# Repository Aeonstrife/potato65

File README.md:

# potato65

PCB, Plate and Case files for Potato65 keyboard.

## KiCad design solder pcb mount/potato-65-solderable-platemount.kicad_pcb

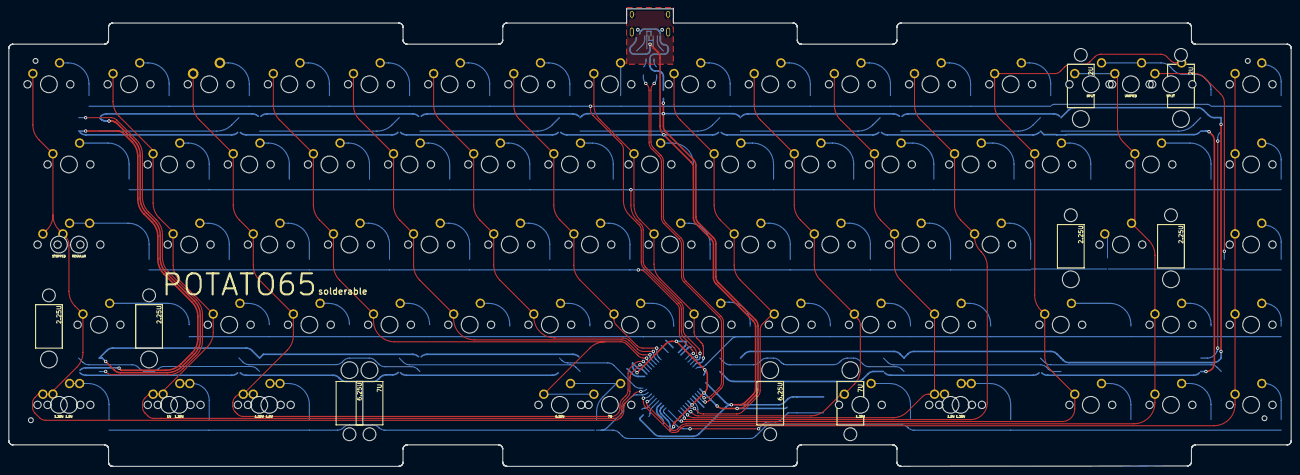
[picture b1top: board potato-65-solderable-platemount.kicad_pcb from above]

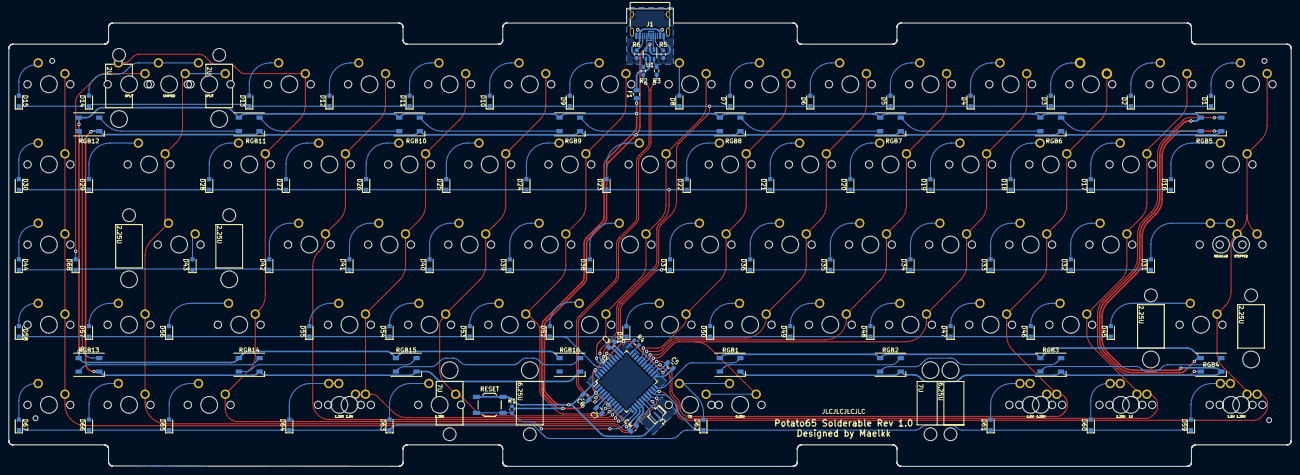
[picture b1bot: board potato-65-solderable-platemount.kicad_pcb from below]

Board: 2 copper layers, 304.8 x 108.7 mm, 172 parts (101 on the bottom side), 120 nets.

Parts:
C3, C4, C5: 0.1uF; C_0805_2012Metric
C6: 10uF; C_0805_2012Metric
C7: 1uF; C_0805_2012Metric
D1, D2, D3, D4, D5, D6, D7, D8, D9, D10, D11, D12, D13, D14, D15, D16, D17, D18, D19, D20, D21, D22, D23, D24, D25, D26, D27, D28, D29, D30, D31, D32, D33, D34, D35, D36, D37, D38, D39, D40, D41, D42, D43, D44, D45, D46, D47, D48, D49, D50, D51, D52, D53, D54, D55, D56, D57, D58, D59, D60, D61, D62, D63, D64, D65, D66, D67, D68: D_Small; D_SOD-323_HandSoldering
F1: Polyfuse_Small; Fuse_0805_2012Metric
J1: USB_C_Receptacle; USB_C_Receptacle_HRO_TYPE-C-31-M-12
MX1, MX2, MX3, MX4, MX5, MX6, MX7, MX8, MX9, MX10, MX11, MX12, MX13, MX13#2, MX13#3, MX13#4, MX15, MX17, MX18, MX19, MX20, MX21, MX22, MX23, MX24, MX25, MX26, MX27, MX28, MX30, MX32, MX33, MX34, MX35, MX36, MX37, MX38, MX39, MX40, MX41, MX42, MX44, MX46, MX47, MX48, MX49, MX50, MX51, MX52, MX53, MX54, MX55, MX57, MX58, MX65, MX66, MX67: MX-NoLED; MXOnly-1U-NoLED
MX14: MX-NoLED; MXOnly-2U-NoLED
MX16, MX29: MX-NoLED; MXOnly-1.5U-NoLED
MX31, MX56: MX-NoLED; MXOnly-1.75U-NoLED
MX43, MX45: MX-NoLED; MXOnly-2.25U-NoLED
MX59, MX59#2, MX60, MX61, MX63, MX64: MX-NoLED; MXOnly-1.25U-NoLED
MX62: MX-NoLED; MXOnly-6.25U-ReversedStabilizers-NoLED
R1, R4: 10k; R_0603_1608Metric
R2, R3: 22; R_0603_1608Metric_Pad0.98x0.95mm_HandSolder
R5, R6: 5.1k; R_0603_1608Metric_Pad0.98x0.95mm_HandSolder
RESET: SW_Push; SW_SPST_TL3342
RGB1, RGB2, RGB3, RGB4, RGB5, RGB6, RGB7, RGB8, RGB9, RGB10, RGB11, RGB12, RGB13, RGB14, RGB15, RGB16: WS2812B; LED_WS2812B_PLCC4_5.0x5.0mm_P3.2mm
U1: USBLC6-2SC6; SOT-23-6
U2: ATmega32U4-AU; TQFP-44_10x10mm_P0.8mm
Y1: 16Mhz; Resonator_SMD_Murata_CSTxExxV-3Pin_3.0x1.1mm

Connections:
+5V: C3.1, C4.1, C5.1, C6.1, F1.1, R1.1, RGB1.1 (VDD), RGB2.1 (VDD), RGB3.1 (VDD), RGB4.1 (VDD), RGB5.1 (VDD), RGB6.1 (VDD), RGB7.1 (VDD), RGB8.1 (VDD), RGB9.1 (VDD), RGB10.1 (VDD), RGB11.1 (VDD), RGB12.1 (VDD), RGB13.1 (VDD), RGB14.1 (VDD), RGB15.1 (VDD), RGB16.1 (VDD), U2.2 (UVCC), U2.7 (VBUS), U2.14 (VCC), U2.24 (AVCC), U2.34 (VCC), U2.44 (AVCC)
COL0: MX1.1 (COL), MX16.1 (COL), MX31.1 (COL), MX45.1 (COL), MX59.1 (COL), MX59#2.1 (COL), U2.21 (PD3)
COL1: MX2.1 (COL), MX13#4.1 (COL), MX17.1 (COL), MX32.1 (COL), MX46.1 (COL), MX60.1 (COL), U2.25 (PD4)
COL2: MX3.1 (COL), MX18.1 (COL), MX33.1 (COL), MX47.1 (COL), MX61.1 (COL), U2.26 (PD6)
COL3: MX4.1 (COL), MX19.1 (COL), MX34.1 (COL), MX48.1 (COL), MX62.1 (COL), U2.27 (PD7)
COL4: MX5.1 (COL), MX20.1 (COL), MX35.1 (COL), MX49.1 (COL), U2.28 (PB4)
COL5: MX6.1 (COL), MX21.1 (COL), MX36.1 (COL), MX50.1 (COL), U2.29 (PB5)
COL6: MX7.1 (COL), MX22.1 (COL), MX37.1 (COL), MX51.1 (COL), U2.30 (PB6)
COL7: MX8.1 (COL), MX23.1 (COL), MX38.1 (COL), MX52.1 (COL), U2.40 (PF1)
COL8: MX9.1 (COL), MX24.1 (COL), MX39.1 (COL), MX53.1 (COL), U2.8 (PB0)
COL9: MX10.1 (COL), MX25.1 (COL), MX40.1 (COL), MX54.1 (COL), MX63.1 (COL), U2.9 (PB1)
COL10: MX11.1 (COL), MX26.1 (COL), MX41.1 (COL), MX55.1 (COL), MX64.1 (COL), U2.10 (PB2)
COL11: MX12.1 (COL), MX27.1 (COL), MX42.1 (COL), U2.11 (PB3)
COL12: MX13.1 (COL), MX13#3.2 (ROW), MX28.1 (COL), MX56.1 (COL), MX65.1 (COL), U2.12 (PB7)
COL13: MX13#2.1 (COL), MX14.1 (COL), MX29.1 (COL), MX43.2 (ROW), MX57.1 (COL), MX66.1 (COL), U2.18 (PD0)
COL14: MX15.1 (COL), MX30.1 (COL), MX44.1 (COL), MX58.1 (COL), MX67.1 (COL), U2.19 (PD1)
D+: J1.A6 (D+), J1.B6 (D+), U1.3 (IO2)
D-: J1.A7 (D-), J1.B7 (D-), U1.1 (IO1)
GND: C3.2, C4.2, C5.2, C6.2, C7.2, J1.A1 (GND), J1.A12 (GND), J1.B1 (GND), J1.B12 (GND), J1.S1 (SHIELD), R4.1, R5.1, R6.1, RESET.1, RGB1.3 (VSS), RGB2.3 (VSS), RGB3.3 (VSS), RGB4.3 (VSS), RGB5.3 (VSS), RGB6.3 (VSS), RGB7.3 (VSS), RGB8.3 (VSS), RGB9.3 (VSS), RGB10.3 (VSS), RGB11.3 (VSS), RGB12.3 (VSS), RGB13.3 (VSS), RGB14.3 (VSS), RGB15.3 (VSS), RGB16.3 (VSS), U1.2 (GND), U2.5 (UGND), U2.15 (GND), U2.23 (GND), U2.35 (GND), U2.43 (GND), Y1.2
unnamed: C7.1, U2.6 (UCAP)
unnamed: D1.2 (A), MX1.2 (ROW)
unnamed: D2.2 (A), MX2.2 (ROW)
unnamed: D3.2 (A), MX3.2 (ROW)
unnamed: D4.2 (A), MX4.2 (ROW)
unnamed: D5.2 (A), MX5.2 (ROW)
unnamed: D6.2 (A), MX6.2 (ROW)
unnamed: D7.2 (A), MX7.2 (ROW)
unnamed: D8.2 (A), MX8.2 (ROW)
unnamed: D9.2 (A), MX9.2 (ROW)
unnamed: D10.2 (A), MX10.2 (ROW)
unnamed: D11.2 (A), MX11.2 (ROW)
unnamed: D12.2 (A), MX12.2 (ROW)
unnamed: D13.2 (A), MX13.2 (ROW)
unnamed: D14.2 (A), MX13#2.2 (ROW), MX14.2 (ROW)
unnamed: D15.2 (A), MX15.2 (ROW)
unnamed: D16.2 (A), MX16.2 (ROW)
unnamed: D17.2 (A), MX17.2 (ROW)
unnamed: D18.2 (A), MX18.2 (ROW)
unnamed: D19.2 (A), MX19.2 (ROW)
unnamed: D20.2 (A), MX20.2 (ROW)
unnamed: D21.2 (A), MX21.2 (ROW)
unnamed: D22.2 (A), MX22.2 (ROW)
unnamed: D23.2 (A), MX23.2 (ROW)
unnamed: D24.2 (A), MX24.2 (ROW)
unnamed: D25.2 (A), MX25.2 (ROW)
unnamed: D26.2 (A), MX26.2 (ROW)
unnamed: D27.2 (A), MX27.2 (ROW)
unnamed: D28.2 (A), MX28.2 (ROW)
unnamed: D29.2 (A), MX29.2 (ROW)
unnamed: D30.2 (A), MX30.2 (ROW)
unnamed: D31.2 (A), MX31.2 (ROW), MX59#2.2 (ROW)
unnamed: D32.2 (A), MX32.2 (ROW)
unnamed: D33.2 (A), MX33.2 (ROW)
unnamed: D34.2 (A), MX34.2 (ROW)
unnamed: D35.2 (A), MX35.2 (ROW)
unnamed: D36.2 (A), MX36.2 (ROW)
unnamed: D37.2 (A), MX37.2 (ROW)
unnamed: D38.2 (A), MX38.2 (ROW)
unnamed: D39.2 (A), MX39.2 (ROW)
unnamed: D40.2 (A), MX40.2 (ROW)
unnamed: D41.2 (A), MX41.2 (ROW)
unnamed: D42.2 (A), MX42.2 (ROW)
unnamed: D43.2 (A), MX43.1 (COL)
unnamed: D44.2 (A), MX44.2 (ROW)
unnamed: D45.2 (A), MX45.2 (ROW)
unnamed: D46.2 (A), MX46.2 (ROW)
unnamed: D47.2 (A), MX47.2 (ROW)
unnamed: D48.2 (A), MX48.2 (ROW)
unnamed: D49.2 (A), MX49.2 (ROW)
unnamed: D50.2 (A), MX50.2 (ROW)
unnamed: D51.2 (A), MX51.2 (ROW)
unnamed: D52.2 (A), MX52.2 (ROW)
unnamed: D53.2 (A), MX53.2 (ROW)
unnamed: D54.2 (A), MX54.2 (ROW)
unnamed: D55.2 (A), MX55.2 (ROW)
unnamed: D56.2 (A), MX56.2 (ROW)
unnamed: D57.2 (A), MX57.2 (ROW)
unnamed: D58.2 (A), MX58.2 (ROW)
unnamed: D59.2 (A), MX59.2 (ROW)
unnamed: D60.2 (A), MX13#4.2 (ROW), MX60.2 (ROW)
unnamed: D61.2 (A), MX61.2 (ROW)
unnamed: D62.2 (A), MX62.2 (ROW)
unnamed: D63.2 (A), MX63.2 (ROW)
unnamed: D64.2 (A), MX64.2 (ROW)
unnamed: D65.2 (A), MX65.2 (ROW)
unnamed: D66.2 (A), MX66.2 (ROW)
unnamed: D67.2 (A), MX67.2 (ROW)
unnamed: J1.A5 (CC1), R5.2
unnamed: J1.B5 (CC2), R6.2
unnamed: R1.2, RESET.2, U2.13 (~RESET)
unnamed: R2.1, U2.4 (D+)
unnamed: R2.2, U1.4 (IO2)
unnamed: R3.1, U2.3 (D-)
unnamed: R3.2, U1.6 (IO1)
unnamed: R4.2, U2.33 (~HWB~/PE2)
unnamed: RGB1.2 (DOUT), RGB2.4 (DIN)
unnamed: RGB2.2 (DOUT), RGB3.4 (DIN)
unnamed: RGB3.2 (DOUT), RGB4.4 (DIN)
unnamed: RGB4.2 (DOUT), RGB5.4 (DIN)
unnamed: RGB5.2 (DOUT), RGB6.4 (DIN)
unnamed: RGB6.2 (DOUT), RGB7.4 (DIN)
unnamed: RGB7.2 (DOUT), RGB8.4 (DIN)
unnamed: RGB8.2 (DOUT), RGB9.4 (DIN)
unnamed: RGB10.2 (DOUT), RGB11.4 (DIN)
unnamed: RGB9.2 (DOUT), RGB10.4 (DIN)
unnamed: RGB11.2 (DOUT), RGB12.4 (DIN)
unnamed: RGB12.2 (DOUT), RGB13.4 (DIN)
unnamed: RGB13.2 (DOUT), RGB14.4 (DIN)
unnamed: RGB14.2 (DOUT), RGB15.4 (DIN)
unnamed: RGB15.2 (DOUT), RGB16.4 (DIN)
unnamed: U2.16 (XTAL2), Y1.3
unnamed: U2.17 (XTAL1), Y1.1
RGBLED: RGB1.4 (DIN), U2.22 (PD5)
ROW0: D1.1 (K), D2.1 (K), D3.1 (K), D4.1 (K), D5.1 (K), D6.1 (K), D7.1 (K), D8.1 (K), D9.1 (K), D10.1 (K), D11.1 (K), D12.1 (K), D13.1 (K), D14.1 (K), D15.1 (K), U2.38 (PF5)
ROW1: D16.1 (K), D17.1 (K), D18.1 (K), D19.1 (K), D20.1 (K), D21.1 (K), D22.1 (K), D23.1 (K), D24.1 (K), D25.1 (K), D26.1 (K), D27.1 (K), D28.1 (K), D29.1 (K), D30.1 (K), U2.39 (PF4)
ROW2: D31.1 (K), D32.1 (K), D33.1 (K), D34.1 (K), D35.1 (K), D36.1 (K), D37.1 (K), D38.1 (K), D39.1 (K), D40.1 (K), D41.1 (K), D42.1 (K), D43.1 (K), D44.1 (K), D68.1 (K), U2.37 (PF6)
ROW3: D45.1 (K), D46.1 (K), D47.1 (K), D48.1 (K), D49.1 (K), D50.1 (K), D51.1 (K), D52.1 (K), D53.1 (K), D54.1 (K), D55.1 (K), D56.1 (K), D57.1 (K), D58.1 (K), U2.41 (PF0)
ROW4: D59.1 (K), D60.1 (K), D61.1 (K), D62.1 (K), D63.1 (K), D64.1 (K), D65.1 (K), D66.1 (K), D67.1 (K), U2.20 (PD2)
VCC: F1.2, J1.A4 (VBUS), J1.A9 (VBUS), J1.B4 (VBUS), J1.B9 (VBUS), U1.5 (VBUS)
net-(d68-pad2): D68.2 (A), MX13#3.1 (COL)

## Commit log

2024-04-02 init files
